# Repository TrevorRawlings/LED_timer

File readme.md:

# Design Overview
## Mechanical

To fit within the waterproof housing the timer is limited to a 44mm diameter cylinder of height 15mm.

The case has been designed using [freeCad](https://www.freecadweb.org/). See the [Configuring FreeCad](#configuring-freecad) 
section below for help setting it up. 

The design files are in the `./freeCad` subdirectory and the finished designs have been 
uploaded to sculpteo ([sculpteo/case2-66](https://www.sculpteo.com/en/print/case2-66/AvhQv5jK) and [sculpteo/bottom-1007](https://www.sculpteo.com/en/print/bottom-1007/qzUkbDYg)).

## Electrical

The unit has a single 2 layer, 40mm diameter PCB.

The electrical design files are in the `./eagle` subfolder. The majority of the components have been sourced from [digiKey](http://www.digikey.com/). See [bill\_of\_materials.xlsx](bill_of_materials.xlsx) for details.

### PCB Manufacture
The circuit boards have been manufactured using [PCBWay](http://www.pcbway.com/).  The steps required to gerber files required by PCBWay are documented in [a blog post](cam_processor/How to generate Gerber from Eagle-SOFTWARE - Share- Hacker - PCBWay.pdf)

TODO: Create a grunt task that automates the process.

Once the .zip archive containing the gerber files has been generated it needs to be uploaded to PCBWay.  The parameters used when submitting an order are [here](cam_processor/pcbway_order_parameters.pdf).

## Software

Software is in the `mplab\LED.X` subfolder.  

#Tools

1. [Cadsoft Eagle PCB Design](https://cadsoft.io/)

   To use the Grunt task the eagle binary will need to be in the [system path](http://www.computerhope.com/issues/ch000549.htm).  For me that meant adding `C:\EAGLE-7.6.0\bin` to the path.
   
1. [Microchip MPLAB X Integrated Development Envrionment (IDE)](http://www.microchip.com/mplab/mplab-x-ide)

1. [MPLAB ICD 3 In-Circuit Debugger](http://www.microchip.com/Developmenttools/ProductDetails.aspx?PartNO=DV164035)

1. [FreeCAD](http://www.freecadweb.org/)
1. [eaglepcb2freecad](https://sourceforge.net/projects/eaglepcb2freecad/?source=typ_redirect)

   A FreeCAD plugin that can import the PCB design from eagle and generate a 3D represenation of the PCB.
      1. Download the [FreeCAD plugin]( https://sourceforge.net/projects/eaglepcb2freecad/?source=typ_redirect)
      1. The .7zachive will need to be extracted. I used the linux tool [dtrx](https://brettcsmith.org/2007/dtrx/)
      1. Follow the instructions within the archive to install the plugin
	  1. eaglepcb2freecad's parts library will need to be configured.  See the [Configuring FreeCAD](#configuring-freecad) section below.

1. [Nodejs](https://nodejs.org/en/)
   Used to download the 3D CAD model libraries used by FreeCAD. 
   
   Download and run the installer. Then at the command prompt:
   ```
   npm install
   ```

2. [Grunt](http://gruntjs.com/getting-started#installing-the-cli)

   Used to automate some tasks.
   
   ```
   npm install -g grunt-cli
   ```

# Configuring FreeCAD

1. Configure eaglepcb2freecad. Open freeCAD and then from the top menu go Edit > Preferences.  In the window the opens select 'PCB' from the list on the left

  * Set the default board thickness to 1.6mm
  * Set the Parts:Paths to include the location of the [freecad_eagle_models](https://github.com/TrevorRawlings/freecad_eagle_models) and [electrical_components](https://github.com/TrevorRawlings/electrical_components) git repositories.  If you have run a `npm install` then two git repos will have been cloned into the node_modules subdirectory:
  
    <project_folder>\node_modules\electrical_components,
	<project_folder>\node_modules\freecad_eagle_models\models_1,
	<project_folder>\node_modules\freecad_eagle_models\models_2,
	<project_folder>\node_modules\freecad_eagle_models\models_3,
	<project_folder>\node_modules\freecad_eagle_models\models_4,
	
  * Import the parts database `eagle2FreecadPartsDb\freecad-pcb_copy.fpcb`
  
    Select 'Printed Circuit Board' `View > Workbench` menu and then click the Assign Models button on the PCB Settings tool bar (see the image below)

	In the window that openc click 'Import Database' from the menu on the left.
    	E:\projects\ALFA_LED\node_modules\electrical_components,E:\projects\ALFA_LED\node_modules\freecad_eagle_models\models_1,E:\projects\ALFA_LED\node_modules\freecad_eagle_models\models_2,E:\projects\ALFA_LED\node_modules\freecad_eagle_models\models_3,E:\projects\ALFA_LED\node_modules\freecad_eagle_models\models_4

	E:\freeCadModels\models_1,E:\freeCadModels\models_2,E:\freeCadModels\models_3,E:\freeCadModels\models_4,E:\freeCadModels\custom

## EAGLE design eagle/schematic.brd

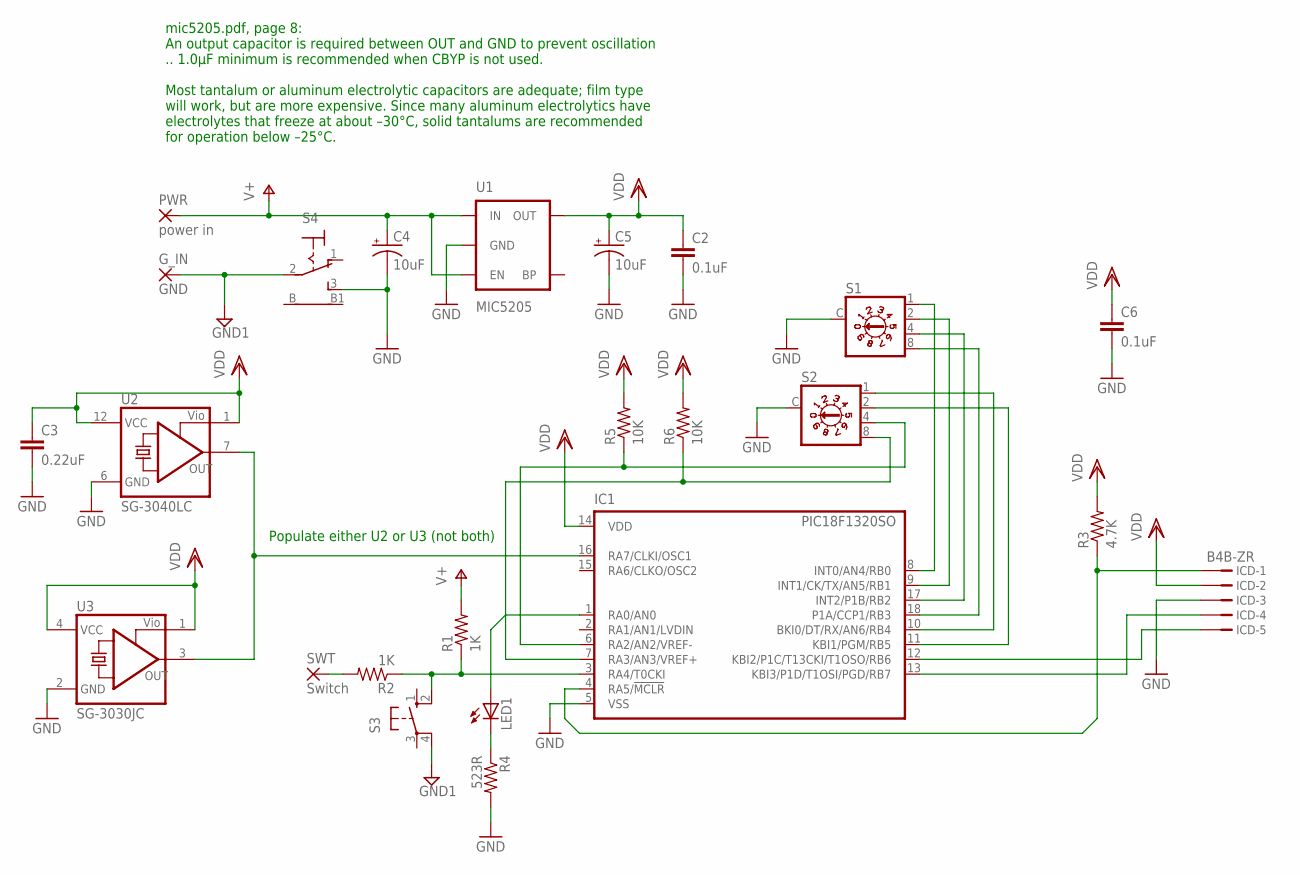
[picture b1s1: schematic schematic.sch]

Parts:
C2, C6: 0.1uF; C2.5-3
C3: 0.22uF; C2.5-3
C4, C5: 10uF; EIA3216
G_IN: GND; 2,15/1,0
IC1: PIC18F1320SO; SO-18W
ICD: B4B-ZR; B5B-EH
LED1: LED3MM
PWR: power in; 2,15/1,0
R1, R2: 1K; 0204V
R3: 4.7K; 0204V
R4: 523R; 0204V
R5, R6: 10K; 0204V
S1, S2: P101
S3: 10-XX; B3F-10XX
S4: C&K_E101; C&K_E101MD1ABE
SWT: Switch; 2,15/1,0
U1: MIC5205; SOT23-5
U2: SG-3040LC; SOJ-12-L
U3: SG-3030JC; JC_TYPE

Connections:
CLK: IC1.16 (RA7/CLKI/OSC1), U2.7 (OUT), U3.3 (OUT)
GND1: G_IN.1, S3.4 (P1), S4.2
unnamed: IC1.3 (RA4/T0CKI), R1.1, R2.1, S3.2 (S1)
unnamed: IC1.10 (BKI0/DT/RX/AN6/RB4), S2.1
unnamed: R2.2, SWT.1
unnamed: IC1.6 (RA2/AN2/VREF-), R5.1, S2.4
unnamed: IC1.7 (RA3/AN3/VREF+), R6.1, S2.8
unnamed: IC1.4 (RA5/!MCLR), ICD.1, R3.1
unnamed: IC1.13 (KBI3/P1D/T1OSI/PGD/RB7), ICD.4
unnamed: IC1.12 (KBI2/P1C/T13CKI/T1OSO/RB6), ICD.5
unnamed: IC1.11 (KBI1/PGM/RB5), S2.2
unnamed: IC1.1 (RA0/AN0), LED1.A
unnamed: LED1.K (C), R4.1
unnamed: C2.2, C3.2, C4.C (-), C5.C (-), C6.2, IC1.5 (VSS), ICD.3, R4.2, S1.C, S2.C, S4.3 (S), U1.2 (GND), U2.6 (GND), U3.2 (GND)
SWITCH_OUT_0: IC1.8 (INT0/AN4/RB0), S1.1
SWITCH_OUT_1: IC1.9 (INT1/CK/TX/AN5/RB1), S1.2
SWITCH_OUT_2: IC1.17 (INT2/P1B/RB2), S1.4
SWITCH_OUT_3: IC1.18 (P1A/CCP1/RB3), S1.8
V+: C4.A (+), PWR.1, R1.2, U1.1 (IN), U1.3 (EN)
VDD: C2.1, C3.1, C5.A (+), C6.1, IC1.14 (VDD), ICD.2, R3.2, R5.2, R6.2, U1.5 (OUT), U2.1 (VIO), U2.12 (VCC), U3.1 (VIO), U3.4 (VCC)

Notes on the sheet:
mic5205.pdf, page 8: An output capacitor is required between OUT and GND to prevent oscillation .. 1.0μF minimum is recommended when CBYP is not used. Most tantalum or aluminum electrolytic capacitors are adequate; film type will work, but are more expensive. Since many aluminum electrolytics have 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
Populate either U2 or U3 (not both)

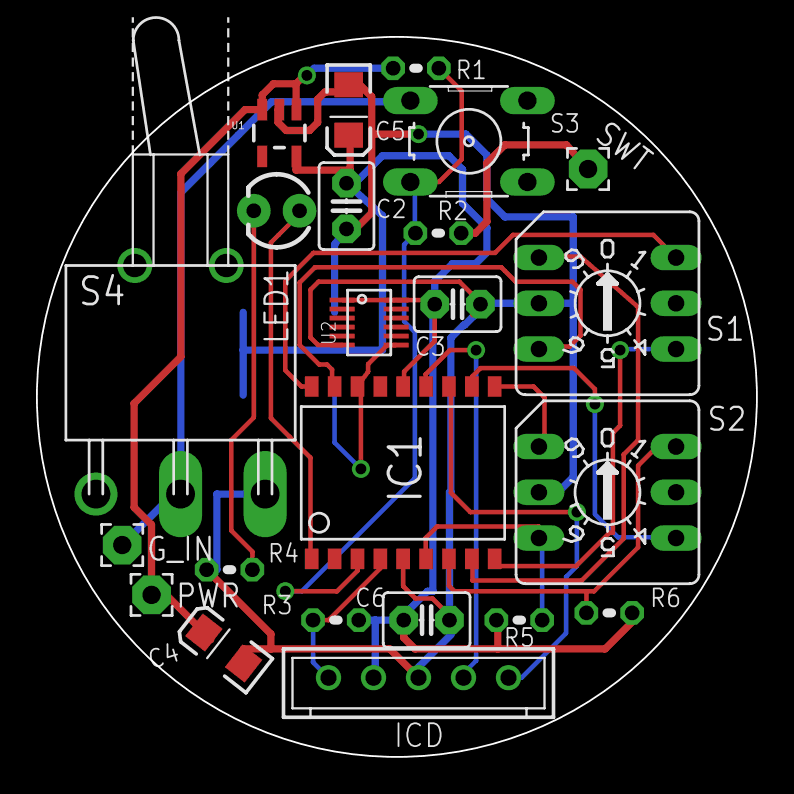
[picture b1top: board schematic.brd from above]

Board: 2 copper layers, 40.0 x 40.0 mm, 24 parts (1 on the bottom side), 20 nets.

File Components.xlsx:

|  | desc | manufacturer/part no | price | number per board | cost per board | source
 | RJ-11 | ICD debugger |  | 3.9 | 0 | 0 | digikey part number 553-2258-ND
 | JST-EH 5 pin | receptacle (housing) | EHR-5 | 0.1 | 0 |  | 455-1003-ND
 |  | socket |  | 0.24 | 1 |  | 455-1614-ND
 |  | crimp connectors | SEH-001T-P0.6 | 0.1 | 0 |  | 455-1042-1-ND
 | ICD |  |  | 200 | 0 | 0 | microchip.com
Microcontroller | PIC18LF1320-I/SO | SOIC, L = low voltage, I = temp range -40 to +85, 'T' would be better but is ou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 |  | 2.95 | 1 | 2.95 | microchip.com | http://www.microchip.com/wwwproducts/en/en010265
 | PIC18LF1320-I/P | PDIP |  | 2.86 | 0 | 0
 | PDIP socket |  |  | 2.0299999999999998 | 0 | 0 | digikey: ED3047-5-ND
U1 | MIC5205 | IC REG LDO 3V 0.15A SOT23-5 |  | 0.4 | 1 | 0.4 | digiKey: 576-1258-1-ND
C4, C5 | Cap 10uF | through hole |  | 0.75 | 0 | 0 | digiKey: 732-6367-1-ND
 |  | surface mount, EIA 3216 (3.2mm x 1.6mm, height 1 mm) |  | 0.53 | 2 | 1.06 | digiKey: 478-8275-1-ND |  | https://en.wikipedia.org/wiki/Surface-mount_technology#Packages
C2, C6 | Cap 0.1 uF | tantalum through hole |  | 0.42 | 2 | 0.84 | digiKey: 478-9315-ND
C3 | Cap >0.1uF (0.22uF) | tantalum through hole |  | 0.42 | 1 | 0.42 | digiKey: 478-8818-ND
 |  | surface mount |  |  |  | 0
LED1 | LED: 1.9V, 2mA | surface mount |  | 0.51 | 0 | 0 | digiKey: 160-1909-1-ND
 |  | through hole, 3.2mm |  | 0.5 | 1 | 0.5 | digiKey: TLLR4400-ND
PCB |  | 40mm diameter |  | 8 | 1 | 8 | pcbway
S4 | toggle switch | DIP switch | Garyhill/76STD01T | 3.44 | 0 | 0 | digiKey: GH7722-ND | Not washable
 |  | through hole toggle switch | E-Switch/100AWSP1T2B4M6RE |  |  |  |  | min order 200
 |  |  | C&K Components/E101MD1ABE | 5.23 | 1 | 5.23 | digiKey: CKN1060-ND
S1, S2 | rotary switch | BCD, 10 position rotary switch, 3-3, through hole | E-Switch/RDMBR10P1T | 2.2799999999999998 | 0 | 0 | digiKey: EG4983-5-ND | min order 1050
 |  |  | Garyhill/EG4983-5-ND | 2.88 | 2 | 5.76 | digiKey: GH7252-ND
U2 | Oscillator | 32.768kHz, 12-SOJ package | Epson/SG-3040LC 32.7680KB3: PURE SN (3.60mm x 2.40mm) | 1.58 | 1 | 1.58 | digiKey: SER3697CT-ND
 |  |  | Epson/SG-3030JC 32.7680 (10.50mm x 5.00mm) | 1.53 |  |  | difiKey: SER3618CT-ND
 |  |  | Epson/SG-3030JF (7.10mm x 4.60mm) | 1.75 | 0 |  | mouser: 732-SG3030JF32.7B3R, digiKey min quantity 250.
S3 | push switch | FSM series, through hole push switch, red |  | 0.1 | 1 | 0.1 | digiKey: 450-1804-ND
R1, R2 | 1K | 1/8 Watt |  |  | 2 | 0.1
R3, R5, R6 | 4.7K | 1/8 Watt |  |  | 3 | 0.1
 | 10K | 1/8 Watt
R4 | 523R | 1/8 Watt |  |  | 1 | 0.1
 |  |  |  |  | total: | 26.839999999999996

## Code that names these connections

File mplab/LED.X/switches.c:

/*
 * File:   switches.c
 * Author: trev_
 *
 * Created on September 11, 2016, 10:47 PM
 */

/******************************************************************************/
/*Files to Include                                                            */
/******************************************************************************/

#if defined(__XC)
    #include <xc.h>         /* XC8 General Include File */
#elif defined(HI_TECH_C)
    #include <htc.h>        /* HiTech General Include File */
#elif defined(__18CXX)
    #include <p18cxxx.h>    /* C18 General Include File */
#endif

#if defined(__XC) || defined(HI_TECH_C)

#include <stdint.h>         /* For uint8_t definition */
#include <stdbool.h>        /* For true/false definition */

#endif
#include "system.h"

#define SWITCH_1_BCD_1 PORTBbits.RB0 // pin also used by A/D channel 4 (AN4)
#define SWITCH_1_BCD_2 PORTBbits.RB1 // pin also used by A/D channel 5 (AN5)
#define SWITCH_1_BCD_4 PORTBbits.RB2 
#define SWITCH_1_BCD_8 PORTBbits.RB3

#define SWITCH_2_BCD_1 PORTBbits.RB4 // pin also used by A/D channel 6 (AN6)
#define SWITCH_2_BCD_2 PORTBbits.RB5
#define SWITCH_2_BCD_4 PORTAbits.RA2 // pin also used by A/D channel 2 (AN2)
#define SWITCH_2_BCD_8 PORTAbits.RA3 // pin also used by A/D channel 3 (AN3)

void configure_switches(void) {
    INTCON2bits.RBPU = 0; // Enable the port B pull ups
    
    // Disable A/D 
    ADCON1bits.PCFG2 = 1;
    ADCON1bits.PCFG3 = 1;
    ADCON1bits.PCFG4 = 1;
    ADCON1bits.PCFG5 = 1;
    ADCON1bits.PCFG6 = 1;
}

char inline convert_bcd_to_byte(char bit1, char bit2, char bit4, char bit8) {
    return bit1 + 
           bit2 * 2 +  
           bit4 * 4 + 
           bit8 * 8;
}

char read_switch1() {
    return convert_bcd_to_byte(!SWITCH_1_BCD_1, 
                               !SWITCH_1_BCD_2, 
                               !SWITCH_1_BCD_4, 
                               !SWITCH_1_BCD_8);
}

char read_switch2() {
    return convert_bcd_to_byte(!SWITCH_2_BCD_1, 
                               !SWITCH_2_BCD_2, 
                               !SWITCH_2_BCD_4, 
                               !SWITCH_2_BCD_8);
}

unsigned int read_switches(void) {
    configure_switches();
    return read_switch1() * 10 + 
           read_switch2();
}

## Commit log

2016-09-26 ignore MPLAB build folders
2016-09-26 Tidy up comments in wait.c
2016-09-28 Replaced ICD board header with a JST-EH connector
2016-09-28 Remove debug code from main.c
2016-09-28 using internal osc and timer2
2016-09-29 Timing using T2 and the external oscillator
2016-09-29 T2 timer driven from internal oscillator (working)
2016-09-30 T2 timer driven from external oscillator (working)
2016-09-30 Using the HSPLL to incease the CPU frequency
2016-09-30 Added larger JC variant of oscillator to the underside of the PCB
2016-09-30 Redo layout of extra oscillator
2016-09-30 Add pdf's of schematic and PCB
2016-09-30 Replace offline webpage with a pdf
2016-09-30 Created a new set of gerber files
2016-09-30 Correct value of C3
2016-09-30 Files missing from the previous commit
2016-10-30 Switch back to EC oscillator mode
2016-10-31 Added pdf specifying pcbway parameters
2016-10-31 Added aditional page to mechanical.vsd with external dimensions of case
2016-11-14 digiKey order 12Nov2016
2016-11-14 Correct wiring of manual push switch, larger holes for ICD, increase U2 footprint
2016-11-14 Create new set of gerber files
2016-12-03 Disable Fail-Safe Clock Monitor
2016-12-03 Added readme
2016-12-11 Added Grunt task to export schematic and pcb images from Eagle
2016-12-12 More updates to the readme and some tidy of the C code
2016-12-12 Added 3D model of PCB
2016-12-18 WIP: Creating a 3D case using freeCad`
2016-12-18 Working on the top surface
2016-12-19 finished outerwall and topsurface
2016-12-19 Added case.stl
2016-12-27 Finished top half of the case
2017-01-01 First version of the case
2017-01-02 Files submitted to sculpteo
2017-02-12 Correct wait delay
2017-02-12 Add links to the sculpteo models
2017-02-12 correct image path
